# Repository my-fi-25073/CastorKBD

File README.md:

# CastorKBD
Castor Split Keyboard

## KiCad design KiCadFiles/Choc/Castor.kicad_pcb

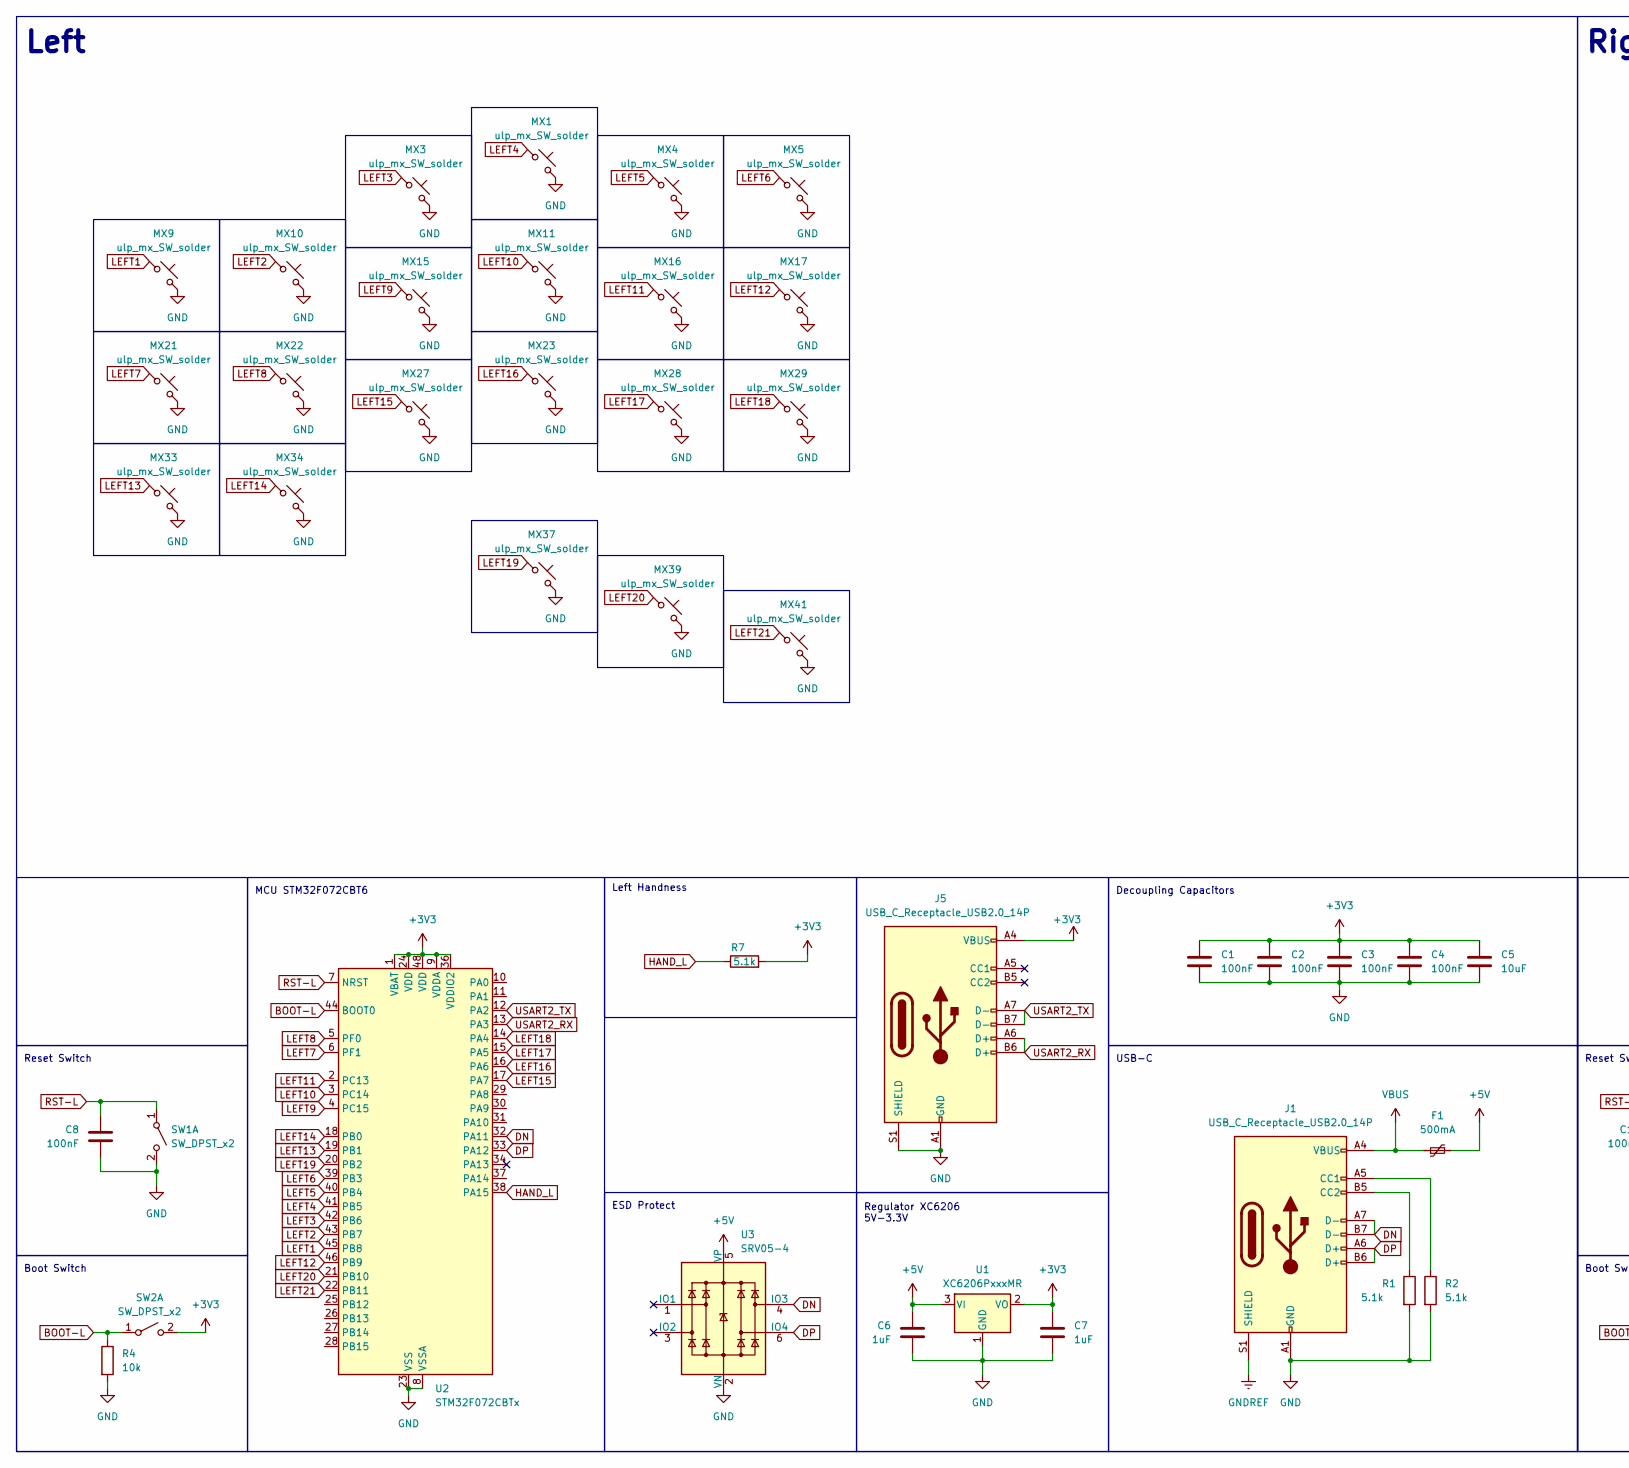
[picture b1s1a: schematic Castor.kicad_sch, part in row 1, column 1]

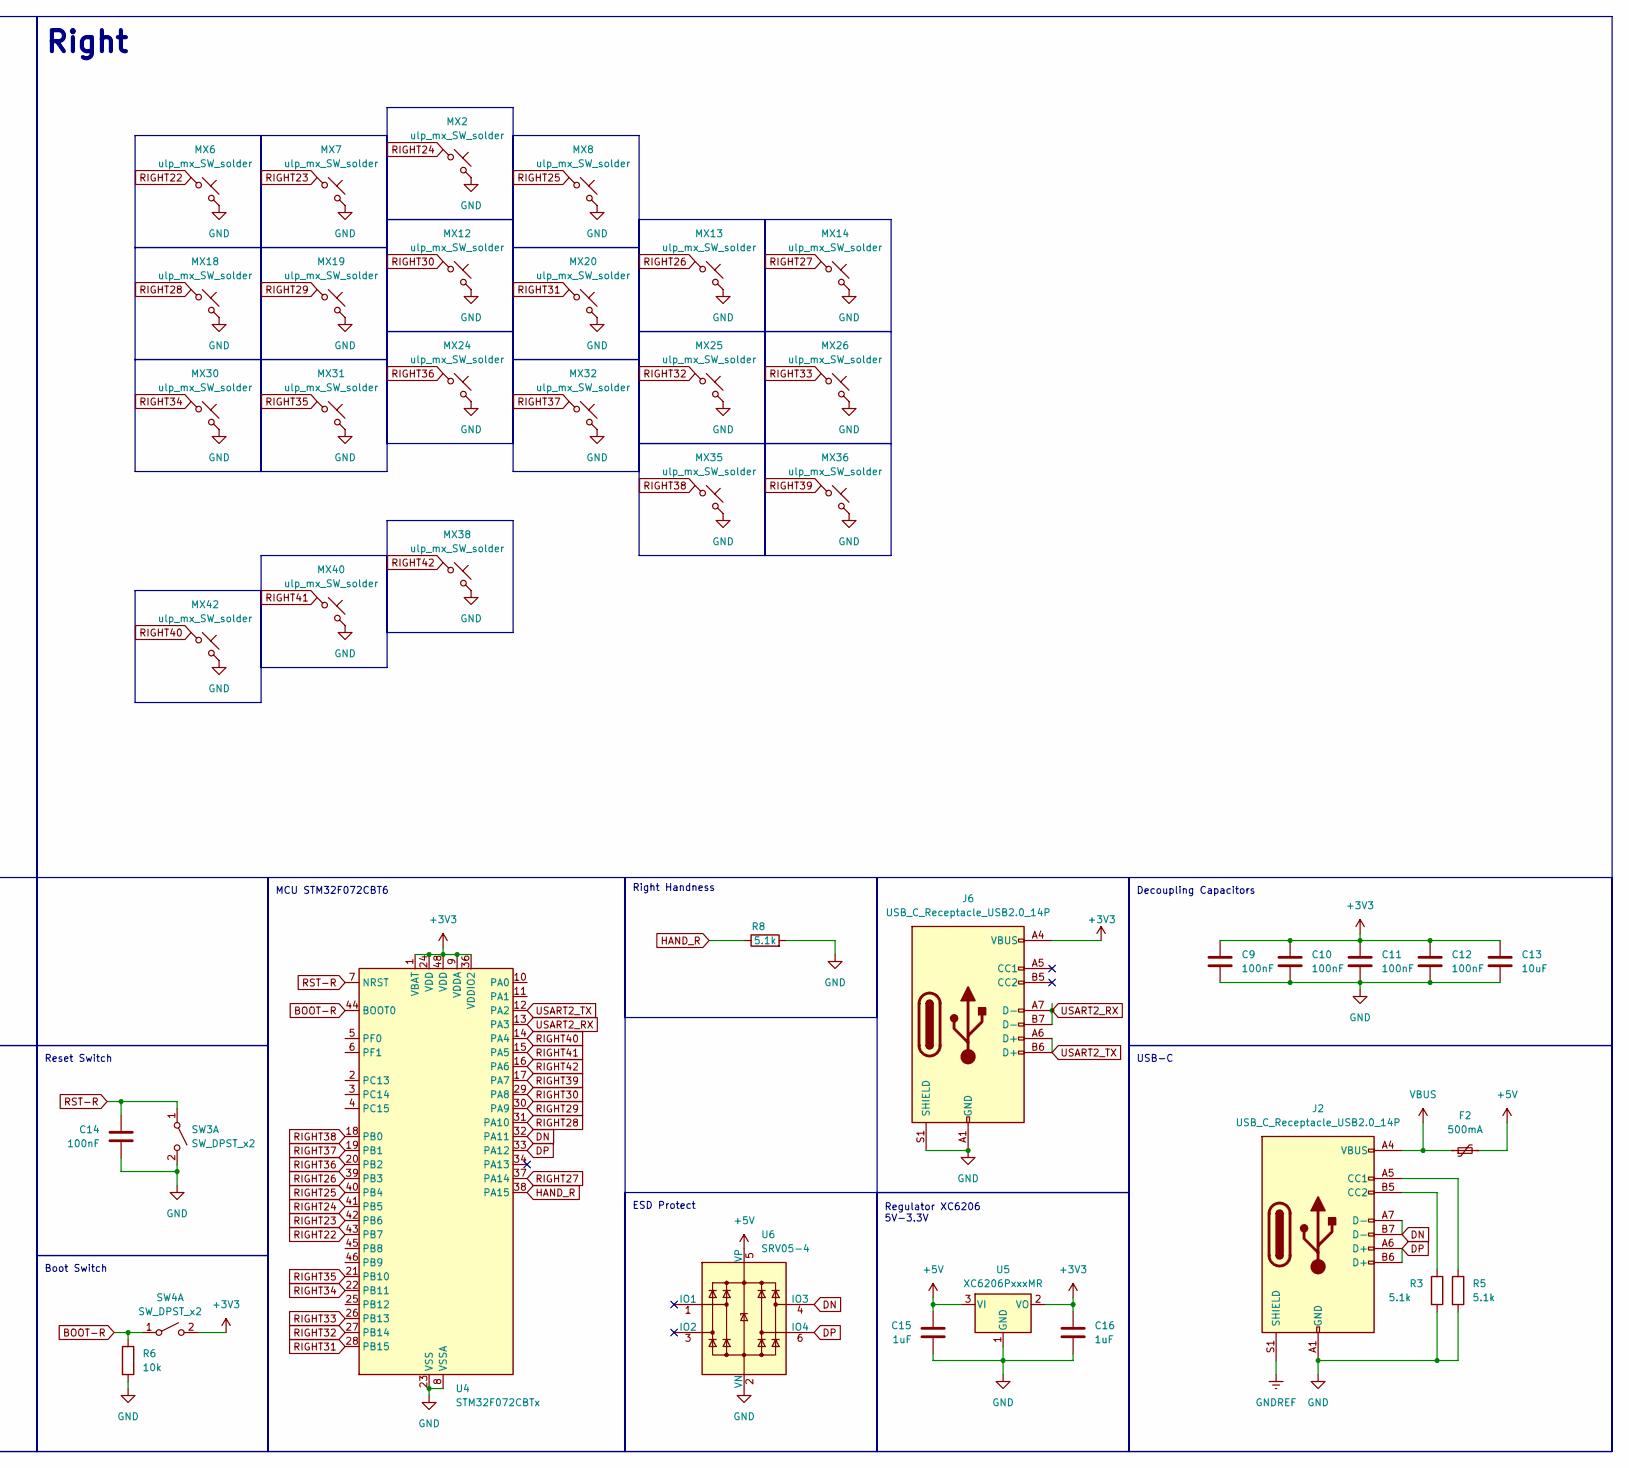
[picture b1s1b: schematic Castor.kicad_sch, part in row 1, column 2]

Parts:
C1, C2, C3, C4, C8, C9, C10, C11, C12, C14: 100nF; C_0402_1005Metric
C5, C13: 10uF; C_0402_1005Metric
C6, C7, C15, C16: 1uF; C_0402_1005Metric
F1, F2: 500mA; Fuse_1206_3216Metric; LCSC C70076
J1, J2, J5, J6: USB_C_Receptacle_USB2.0_14P; USB_C_Receptacle_HRO_TYPE-C-31-M-12; MPN C2894897
MX1, MX2, MX3, MX4, MX5, MX6, MX7, MX8, MX9, MX10, MX11, MX12, MX13, MX14, MX15, MX16, MX17, MX18, MX19, MX20, MX21, MX22, MX23, MX24, MX25, MX26, MX27, MX28, MX29, MX30, MX31, MX32, MX33, MX34, MX35, MX36, MX37, MX38, MX39, MX40, MX41, MX42: ulp_mx_SW_solder; SW_choc_v1+v2_1u
R1, R2, R3, R5, R7, R8: 5.1k; R_0402_1005Metric
R4, R6: 10k; R_0402_1005Metric
SW1, SW2, SW3, SW4: SW_DPST_x2; SW_Push_1P1T_XKB_TS-1187A; MPN C318884
U1, U5: XC6206PxxxMR; SOT-23-3; MPN C5148692
U2, U4: STM32F072CBTx; LQFP-48_7x7mm_P0.5mm; MPN C81720
U3, U6: SRV05-4; SOT-23-6; MPN C7420376

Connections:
+3V3: C1.1, C2.1, C3.1, C4.1, C5.1, C7.1, C9.1, C10.1, C11.1, C12.1, C13.1, C16.1, J5.A4 (VBUS), J5.A9 (VBUS), J5.B4 (VBUS), J5.B9 (VBUS), J6.A4 (VBUS), J6.A9 (VBUS), J6.B4 (VBUS), J6.B9 (VBUS), R7.2, SW2.2 (B), SW4.2 (B), U1.2 (VO), U2.1 (VBAT), U2.9 (VDDA), U2.24 (VDD), U2.36 (VDDIO2), U2.48 (VDD), U4.1 (VBAT), U4.9 (VDDA), U4.24 (VDD), U4.36 (VDDIO2), U4.48 (VDD), U5.2 (VO)
+5V: C6.1, C15.1, F1.2, F2.2, U1.3 (VI), U3.5 (VP), U5.3 (VI), U6.5 (VP)
BOOT-L: R4.1, SW2.1 (A), U2.44 (BOOT0)
BOOT-R: R6.1, SW4.1 (A), U4.44 (BOOT0)
DN: J1.A7 (D-), J1.B7 (D-), J2.A7 (D-), J2.B7 (D-), U2.32 (PA11), U3.4 (IO3), U4.32 (PA11), U6.4 (IO3)
DP: J1.A6 (D+), J1.B6 (D+), J2.A6 (D+), J2.B6 (D+), U2.33 (PA12), U3.6 (IO4), U4.33 (PA12), U6.6 (IO4)
GND: C1.2, C2.2, C3.2, C4.2, C5.2, C6.2, C7.2, C8.2, C9.2, C10.2, C11.2, C12.2, C13.2, C14.2, C15.2, C16.2, J1.A1 (GND), J1.A12 (GND), J1.B1 (GND), J1.B12 (GND), J2.A1 (GND), J2.A12 (GND), J2.B1 (GND), J2.B12 (GND), J5.A1 (GND), J5.A12 (GND), J5.B1 (GND), J5.B12 (GND), J5.S1 (SHIELD), J6.A1 (GND), J6.A12 (GND), J6.B1 (GND), J6.B12 (GND), J6.S1 (SHIELD), MX1.2, MX2.2, MX3.2, MX4.2, MX5.2, MX6.2, MX7.2, MX8.2, MX9.2, MX10.2, MX11.2, MX12.2, MX13.2, MX14.2, MX15.2, MX16.2, MX17.2, MX18.2, MX19.2, MX20.2, MX21.2, MX22.2, MX23.2, MX24.2, MX25.2, MX26.2, MX27.2, MX28.2, MX29.2, MX30.2, MX31.2, MX32.2, MX33.2, MX34.2, MX35.2, MX36.2, MX37.2, MX38.2, MX39.2, MX40.2, MX41.2, MX42.2, R1.2, R2.2, R3.2, R4.2, R5.2, R6.2, R8.2, SW1.2 (B), SW3.2 (B), U1.1 (GND), U2.8 (VSSA), U2.23 (VSS), U2.35 (VSS), U2.47 (VSS), U3.2 (VN), U4.8 (VSSA), U4.23 (VSS), U4.35 (VSS), U4.47 (VSS), U5.1 (GND), U6.2 (VN)
GNDREF: J1.S1 (SHIELD), J2.S1 (SHIELD)
HAND_L: R7.1, U2.38 (PA15)
HAND_R: R8.1, U4.38 (PA15)
LEFT1: MX9.1, U2.45 (PB8)
LEFT2: MX10.1, U2.43 (PB7)
LEFT3: MX3.1, U2.42 (PB6)
LEFT4: MX1.1, U2.41 (PB5)
LEFT5: MX4.1, U2.40 (PB4)
LEFT6: MX5.1, U2.39 (PB3)
LEFT7: MX21.1, U2.6 (PF1)
LEFT8: MX22.1, U2.5 (PF0)
LEFT9: MX15.1, U2.4 (PC15)
LEFT10: MX11.1, U2.3 (PC14)
LEFT11: MX16.1, U2.2 (PC13)
LEFT12: MX17.1, U2.46 (PB9)
LEFT13: MX33.1, U2.19 (PB1)
LEFT14: MX34.1, U2.18 (PB0)
LEFT15: MX27.1, U2.17 (PA7)
LEFT16: MX23.1, U2.16 (PA6)
LEFT17: MX28.1, U2.15 (PA5)
LEFT18: MX29.1, U2.14 (PA4)
LEFT19: MX37.1, U2.20 (PB2)
LEFT20: MX39.1, U2.21 (PB10)
LEFT21: MX41.1, U2.22 (PB11)
unnamed: J1.A5 (CC1), R2.1
unnamed: J1.B5 (CC2), R1.1
unnamed: J2.A5 (CC1), R5.1
unnamed: J2.B5 (CC2), R3.1
RIGHT22: MX6.1, U4.43 (PB7)
RIGHT23: MX7.1, U4.42 (PB6)
RIGHT24: MX2.1, U4.41 (PB5)
RIGHT25: MX8.1, U4.40 (PB4)
RIGHT26: MX13.1, U4.39 (PB3)
RIGHT27: MX14.1, U4.37 (PA14)
RIGHT28: MX18.1, U4.31 (PA10)
RIGHT29: MX19.1, U4.30 (PA9)
RIGHT30: MX12.1, U4.29 (PA8)
RIGHT31: MX20.1, U4.28 (PB15)
RIGHT32: MX25.1, U4.27 (PB14)
RIGHT33: MX26.1, U4.26 (PB13)
RIGHT34: MX30.1, U4.22 (PB11)
RIGHT35: MX31.1, U4.21 (PB10)
RIGHT36: MX24.1, U4.20 (PB2)
RIGHT37: MX32.1, U4.19 (PB1)
RIGHT38: MX35.1, U4.18 (PB0)
RIGHT39: MX36.1, U4.17 (PA7)
RIGHT40: MX42.1, U4.14 (PA4)
RIGHT41: MX40.1, U4.15 (PA5)
RIGHT42: MX38.1, U4.16 (PA6)
RST-L: C8.1, SW1.1 (A), U2.7 (NRST)
RST-R: C14.1, SW3.1 (A), U4.7 (NRST)
USART2_RX: J5.A6 (D+), J5.B6 (D+), J6.A7 (D-), J6.B7 (D-), U2.13 (PA3), U4.13 (PA3)
USART2_TX: J5.A7 (D-), J5.B7 (D-), J6.A6 (D+), J6.B6 (D+), U2.12 (PA2), U4.12 (PA2)
VBUS: F1.1, F2.1, J1.A4 (VBUS), J1.A9 (VBUS), J1.B4 (VBUS), J1.B9 (VBUS), J2.A4 (VBUS), J2.A9 (VBUS), J2.B4 (VBUS), J2.B9 (VBUS)

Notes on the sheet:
ESD Protect
Left
Regulator XC6206 5V-3.3V
Boot Switch
Left Handness
Decoupling Capacitors
USB-C
Reset Switch
Right
MCU STM32F072CBT6
Right Handness

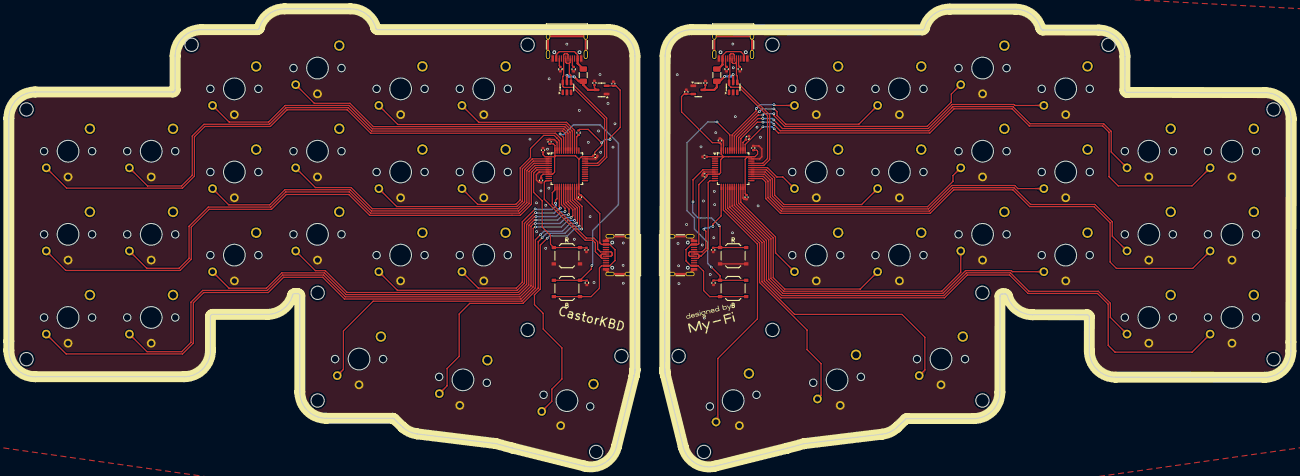
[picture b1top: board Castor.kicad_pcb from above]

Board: 2 copper layers, 293.8 x 105.0 mm, 82 parts (0 on the bottom side), 61 nets.

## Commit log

2025-10-13 Initial commit of castor_kbd keyboard files, including configuration (keyboard.json), keymap (keymap.c), KiCad PCB and schematic files, and a README for setup instructions.
2025-10-13 Update KiCad project files for Castor: added 3D viewports, IPC2581 settings, and enhanced ERC configurations. Updated schematic with new USB-C and audio jack components, including detailed properties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
2025-10-16 Enhance KiCad project files for Castor: updated PCB layout with detailed layer configurations, added new components including a 1N4148WS diode with properties, and improved schematic with additional 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
2025-10-16 Add new DXF files for Castor project: introduced Castor-Edge_Cuts.dxf and Castor_border.dxf, while removing obsolete Edge_Cuts and User_2 DXF files. Updated PCB layout with new arc and line geometrie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
2025-10-23 Refactor KiCad project files for Castor: updated PCB layout with new component footprints and adjusted positions for resistors and capacitors. Removed obsolete audio jack symbol from schematic and ad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
2025-11-12 Update KiCad project files for Castor: added new global labels for RST and BOOT signals in the schematic, adjusted their positions, and removed obsolete labels. Updated PCB layout with new net connec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
2025-11-12 Update PCB layout for Castor: modified existing gr_circle elements' positions and added new gr_circle elements for edge cuts, enhancing the design's clarity and structure. Adjusted stroke properties 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
2025-11-18 updated PCB layout by rearranging net connections and correcting net labels for improved clarity. Added new global labels for BOOT and RST signals in the schematic while removing obsolete labels. Enh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
2025-12-07 Update KiCad project files for Castor: added new DRC exclusions in the project configuration, adjusted solder mask clearance, and refined global labels in the schematic for improved clarity. Updated 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
2025-12-07 Update KiCad project files for Castor: modified PCB layout with new UUIDs for various elements, adjusted layer selection and plot parameters, and added a new user-defined rectangle layer. Updated pro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
2025-12-08 Update KiCad project files for Castor: cleared DRC exclusions in the project configuration for improved design integrity. Updated .gitignore to include new files for extraction and fabrication toolki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
2025-12-08 Add configuration and matrix layout for Castor keyboard: created config.h for split keyboard settings, updated keyboard.json with new matrix pin configurations and split functionality, and adjusted l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
2025-12-08 Add custom keycode handling for Castor keyboard: created my_keycode.c and my_keycode.h for custom key mappings and OS-specific functionality, updated keymap.c to integrate new keycodes, and modified 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
2025-12-08 Add USART full-duplex configuration for Castor keyboard: updated config.h with USART settings, created halconf.h for serial support, and added mcuconf.h to enable USART2. Adjusted keyboard.json to re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
2025-12-08 Update keyboard configuration and add VIA support for Castor KBD: modified keyboard.json to include a GitHub URL and updated USB identifiers. Added new via.json file for layout and custom keycode def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
2025-12-16 Enhance Castor keyboard configuration: removed USB suspend wakeup delay, added USART PAL mode settings, and enabled split watchdog for improved performance. Updated rules.mk to support serial transpo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
2025-12-19 Added Choc LP version of Castor KBD
2025-12-20 Update KiCad project files for Castor keyboard: added new PCB layout files for ULPCastor and updated existing files with new UUIDs and configurations. Enhanced .gitignore to include additional extrac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
